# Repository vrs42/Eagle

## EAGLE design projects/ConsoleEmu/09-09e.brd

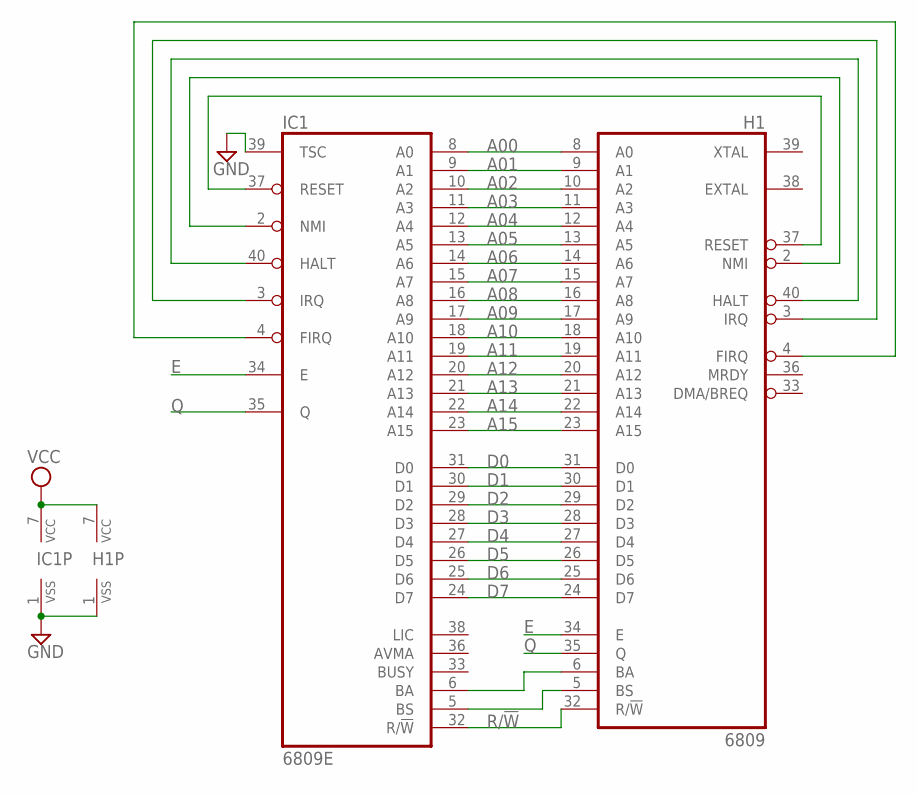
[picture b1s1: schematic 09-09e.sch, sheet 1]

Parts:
H1: 6809; DIL40
IC1: 6809E; DIL40

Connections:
A00: H1.8 (A0), IC1.8 (A0)
A01: H1.9 (A1), IC1.9 (A1)
A02: H1.10 (A2), IC1.10 (A2)
A03: H1.11 (A3), IC1.11 (A3)
A04: H1.12 (A4), IC1.12 (A4)
A05: H1.13 (A5), IC1.13 (A5)
A06: H1.14 (A6), IC1.14 (A6)
A07: H1.15 (A7), IC1.15 (A7)
A08: H1.16 (A8), IC1.16 (A8)
A09: H1.17 (A9), IC1.17 (A9)
A10: H1.18 (A10), IC1.18 (A10)
A11: H1.19 (A11), IC1.19 (A11)
A12: H1.20 (A12), IC1.20 (A12)
A13: H1.21 (A13), IC1.21 (A13)
A14: H1.22 (A14), IC1.22 (A14)
A15: H1.23 (A15), IC1.23 (A15)
D0: H1.31 (D0), IC1.31 (D0)
D1: H1.30 (D1), IC1.30 (D1)
D2: H1.29 (D2), IC1.29 (D2)
D3: H1.28 (D3), IC1.28 (D3)
D4: H1.27 (D4), IC1.27 (D4)
D5: H1.26 (D5), IC1.26 (D5)
D6: H1.25 (D6), IC1.25 (D6)
D7: H1.24 (D7), IC1.24 (D7)
E: H1.34 (E), IC1.34 (E); also elsewhere on the board
GND: H1.1 (VSS), IC1.1 (VSS), IC1.39 (TSC); also elsewhere on the board
unnamed: H1.5 (BS), IC1.5 (BS)
unnamed: H1.6 (BA), IC1.6 (BA)
unnamed: H1.37 (RESET), IC1.37 (RESET)
unnamed: H1.2 (NMI), IC1.2 (NMI)
unnamed: H1.40 (HALT), IC1.40 (HALT)
unnamed: H1.3 (IRQ), IC1.3 (IRQ)
unnamed: H1.4 (FIRQ), IC1.4 (FIRQ)
Q: H1.35 (Q), IC1.35 (Q); also elsewhere on the board
R/!W: H1.32 (R/!W), IC1.32 (R/!W)
VCC: H1.7 (VCC), IC1.7 (VCC); also elsewhere on the board

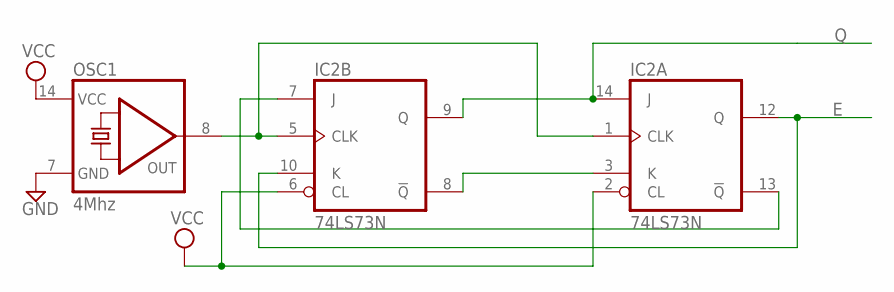
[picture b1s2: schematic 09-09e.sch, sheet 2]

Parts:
IC2: 74LS73N; DIL14
OSC1: 4Mhz; DIL14S

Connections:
E: IC2.10 (K), IC2.12 (Q); also elsewhere on the board
GND: IC2.11 (GND), OSC1.7 (GND); also elsewhere on the board
unnamed: IC2.1 (CLK), IC2.5 (CLK), OSC1.8 (OUT)
unnamed: IC2.3 (K), IC2.8 (!Q)
unnamed: IC2.7 (J), IC2.13 (!Q)
Q: IC2.9 (Q), IC2.14 (J); also elsewhere on the board
VCC: IC2.2 (CL), IC2.4 (VCC), IC2.6 (CL), OSC1.14 (VCC); also elsewhere on the board

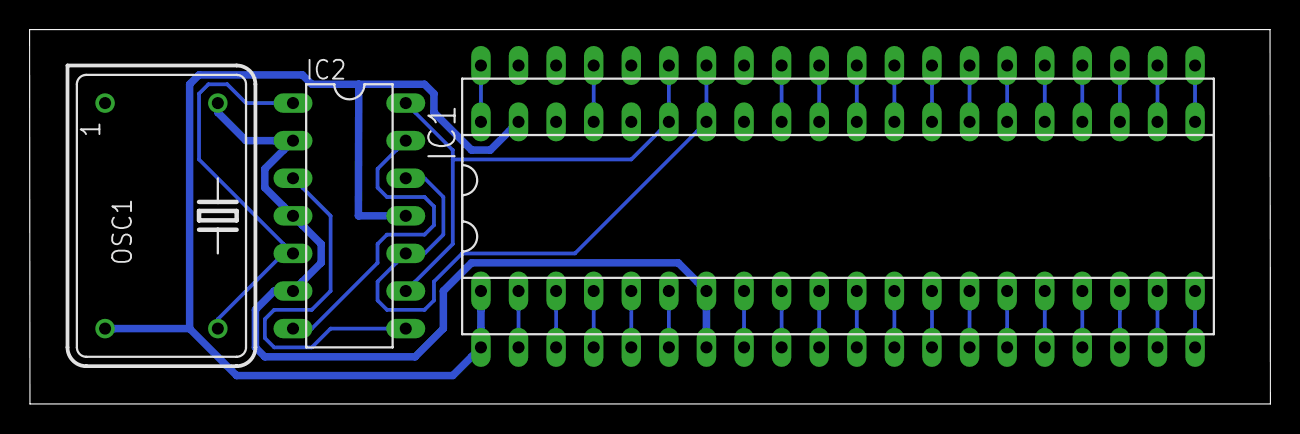
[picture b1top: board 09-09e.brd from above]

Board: 2 copper layers, 83.9 x 25.3 mm, 4 parts (0 on the bottom side), 39 nets.

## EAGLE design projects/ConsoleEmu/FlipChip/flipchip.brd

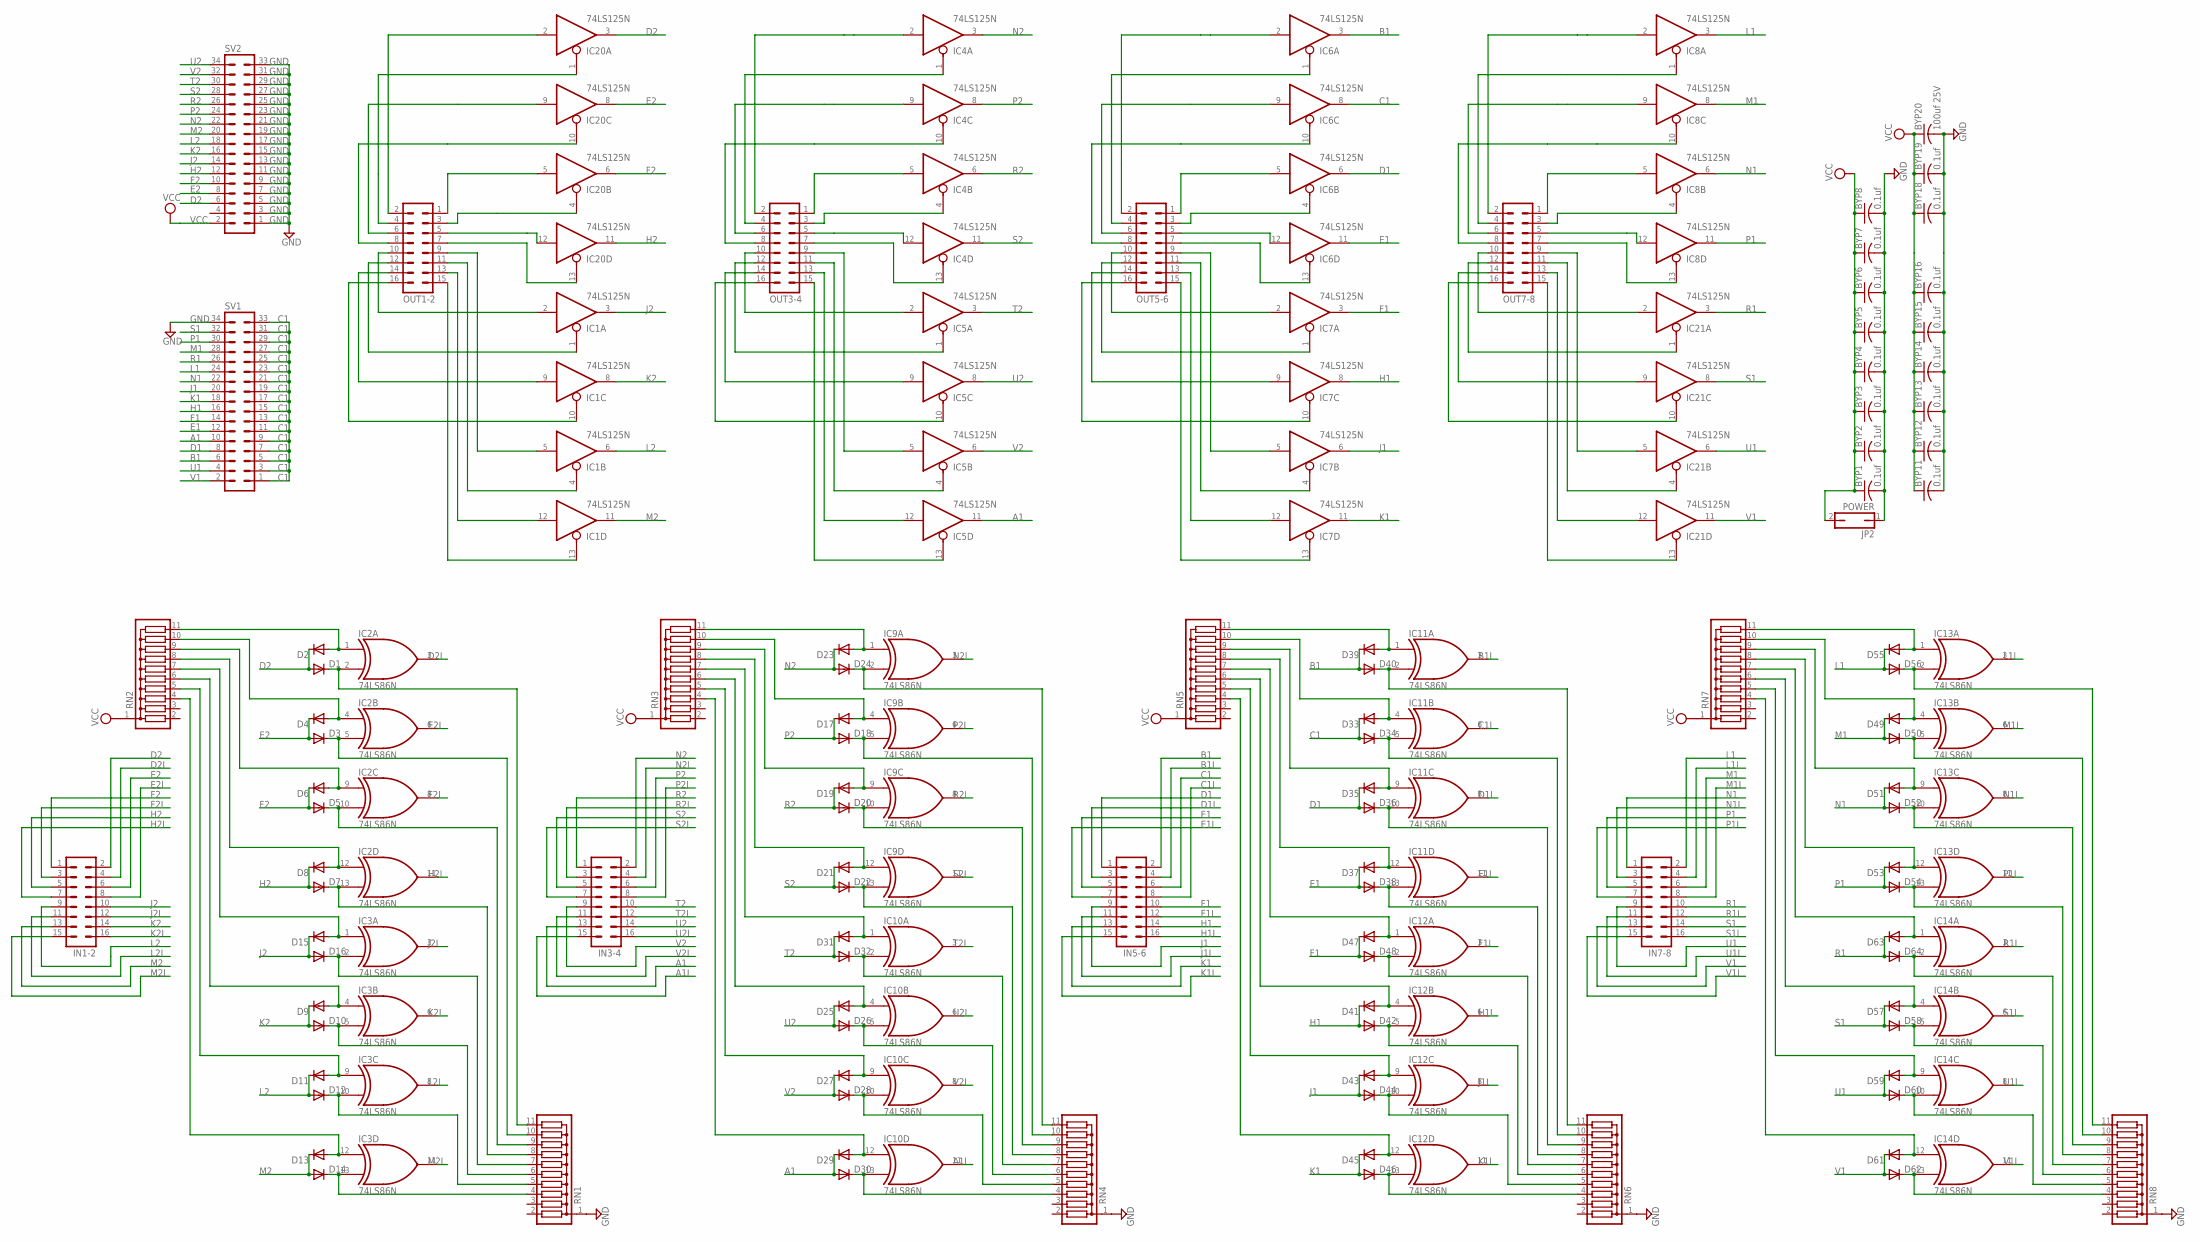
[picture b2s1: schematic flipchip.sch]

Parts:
BYP1, BYP2, BYP3, BYP4, BYP5, BYP6, BYP7, BYP8, BYP11, BYP12, BYP13, BYP14, BYP15, BYP16, BYP18, BYP19: 0.1uf; C050-025X075
BYP20: 100uf 25V; C150-064X183
D1, D2, D3, D4, D5, D6, D7, D8, D9, D10, D11, D12, D13, D14, D15, D16, D17, D18, D19, D20, D21, D22, D23, D24, D25, D26, D27, D28, D29, D30, D31, D32, D33, D34, D35, D36, D37, D38, D39, D40, D41, D42, D43, D44, D45, D46, D47, D48, D49, D50, D51, D52, D53, D54, D55, D56, D57, D58, D59, D60, D61, D62, D63, D64: DIODE-D-2.5; D-2.5
IC1, IC4, IC5, IC6, IC7, IC8, IC20, IC21: 74LS125N; DIL14
IC2, IC3, IC9, IC10, IC11, IC12, IC13, IC14: 74LS86N; DIL14
IN1-2, IN3-4, IN5-6, IN7-8: MA08-2
JP2: POWER; JP1
OUT1-2, OUT3-4, OUT5-6, OUT7-8: MA08-2
RN1, RN2, RN3, RN4, RN5, RN6, RN7, RN8: G10R; SIL11
SV1, SV2: MA17-2

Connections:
A1: D29.C, D30.A, IC5.11 (O), IN3-4.13, SV1.10
A1I: IC10.11 (O), IN3-4.15
B1: D39.C, D40.A, IC6.3 (O), IN5-6.2, SV1.6
B1I: IC11.3 (O), IN5-6.4
C1: D33.C, D34.A, IC6.8 (O), IN5-6.6, SV1.1, SV1.3, SV1.5, SV1.7, SV1.9, SV1.11, SV1.13, SV1.15, SV1.17, SV1.19, SV1.21, SV1.23, SV1.25, SV1.27, SV1.29, SV1.31, SV1.33
C1I: IC11.6 (O), IN5-6.8
D1: D35.C, D36.A, IC6.6 (O), IN5-6.1, SV1.8
D1I: IC11.8 (O), IN5-6.3
D2: D1.A, D2.C, IC20.3 (O), IN1-2.2, SV2.6
D2I: IC2.3 (O), IN1-2.4
E1: D37.C, D38.A, IC6.11 (O), IN5-6.5, SV1.12
E1I: IC11.11 (O), IN5-6.7
E2: D3.A, D4.C, IC20.8 (O), IN1-2.6, SV2.8
E2I: IC2.6 (O), IN1-2.8
F1: D47.C, D48.A, IC7.3 (O), IN5-6.10, SV1.14
F1I: IC12.3 (O), IN5-6.12
F2: D5.A, D6.C, IC20.6 (O), IN1-2.1, SV2.10
F2I: IC2.8 (O), IN1-2.3
GND: BYP1.2, BYP2.2, BYP3.2, BYP4.2, BYP5.2, BYP6.2, BYP7.2, BYP8.2, BYP11.2, BYP12.2, BYP13.2, BYP14.2, BYP15.2, BYP16.2, BYP18.2, BYP19.2, BYP20.2, IC1.7 (GND), IC2.7 (GND), IC3.7 (GND), IC4.7 (GND), IC5.7 (GND), IC6.7 (GND), IC7.7 (GND), IC8.7 (GND), IC9.7 (GND), IC10.7 (GND), IC11.7 (GND), IC12.7 (GND), IC13.7 (GND), IC14.7 (GND), IC20.7 (GND), IC21.7 (GND), JP2.1, RN1.1, RN4.1, RN6.1, RN8.1, SV1.34, SV2.1, SV2.3, SV2.5, SV2.7, SV2.9, SV2.11, SV2.13, SV2.15, SV2.17, SV2.19, SV2.21, SV2.23, SV2.25, SV2.27, SV2.29, SV2.31, SV2.33
H1: D41.C, D42.A, IC7.8 (O), IN5-6.14, SV1.16
H1I: IC12.6 (O), IN5-6.16
H2: D7.A, D8.C, IC20.11 (O), IN1-2.5, SV2.12
H2I: IC2.11 (O), IN1-2.7
J1: D43.C, D44.A, IC7.6 (O), IN5-6.9, SV1.20
J1I: IC12.8 (O), IN5-6.11
J2: D15.C, D16.A, IC1.3 (O), IN1-2.10, SV2.14
J2I: IC3.3 (O), IN1-2.12
K1: D45.C, D46.A, IC7.11 (O), IN5-6.13, SV1.18
K1I: IC12.11 (O), IN5-6.15
K2: D9.C, D10.A, IC1.8 (O), IN1-2.14, SV2.16
K2I: IC3.6 (O), IN1-2.16
L1: D55.C, D56.A, IC8.3 (O), IN7-8.2, SV1.24
L1I: IC13.3 (O), IN7-8.4
L2: D11.C, D12.A, IC1.6 (O), IN1-2.9, SV2.18
L2I: IC3.8 (O), IN1-2.11
M1: D49.C, D50.A, IC8.8 (O), IN7-8.6, SV1.28
M1I: IC13.6 (O), IN7-8.8
M2: D13.C, D14.A, IC1.11 (O), IN1-2.13, SV2.20
M2I: IC3.11 (O), IN1-2.15
N1: D51.C, D52.A, IC8.6 (O), IN7-8.1, SV1.22
N1I: IC13.8 (O), IN7-8.3
N2: D23.C, D24.A, IC4.3 (O), IN3-4.2, SV2.22
N2I: IC9.3 (O), IN3-4.4
unnamed: D24.C, IC9.2 (I1), RN4.11
unnamed: D23.A, IC9.1 (I0), RN3.11
unnamed: D1.C, IC2.2 (I1), RN1.11
unnamed: D2.A, IC2.1 (I0), RN2.11
unnamed: D18.C, IC9.5 (I1), RN4.10
unnamed: D3.C, IC2.5 (I1), RN1.10
unnamed: D17.A, IC9.4 (I0), RN3.10
unnamed: D19.A, IC9.9 (I0), RN3.9
unnamed: D21.A, IC9.12 (I0), RN3.8
unnamed: D31.A, IC10.1 (I0), RN3.7
unnamed: D25.A, IC10.4 (I0), RN3.6
unnamed: D27.A, IC10.9 (I0), RN3.5
unnamed: D29.A, IC10.12 (I0), RN3.4
unnamed: D28.C, IC10.10 (I1), RN4.5
unnamed: D20.C, IC9.10 (I1), RN4.9
unnamed: D22.C, IC9.13 (I1), RN4.8
unnamed: D32.C, IC10.2 (I1), RN4.7
unnamed: D26.C, IC10.5 (I1), RN4.6
unnamed: D30.C, IC10.13 (I1), RN4.4
unnamed: D40.C, IC11.2 (I1), RN6.11
unnamed: D4.A, IC2.4 (I0), RN2.10
unnamed: D39.A, IC11.1 (I0), RN5.11
unnamed: D5.C, IC2.10 (I1), RN1.9
unnamed: D6.A, IC2.9 (I0), RN2.9
unnamed: D34.C, IC11.5 (I1), RN6.10
unnamed: IC6.2 (I), OUT5-6.2
unnamed: IC4.5 (I), OUT3-4.1
unnamed: IC4.4 (OE), OUT3-4.3
unnamed: IC4.12 (I), OUT3-4.5
unnamed: IC4.13 (OE), OUT3-4.7
unnamed: IC4.1 (OE), OUT3-4.4
unnamed: IC4.9 (I), OUT3-4.6
unnamed: IC4.2 (I), OUT3-4.2
unnamed: IC4.10 (OE), OUT3-4.8
unnamed: IC20.5 (I), OUT1-2.1
unnamed: IC20.4 (OE), OUT1-2.3
unnamed: IC20.12 (I), OUT1-2.5
unnamed: IC20.13 (OE), OUT1-2.7
unnamed: IC20.2 (I), OUT1-2.2
unnamed: IC20.1 (OE), OUT1-2.4
unnamed: IC20.9 (I), OUT1-2.6
unnamed: IC20.10 (OE), OUT1-2.8
unnamed: IC1.13 (OE), OUT1-2.15
unnamed: IC1.12 (I), OUT1-2.13
unnamed: IC1.4 (OE), OUT1-2.11
unnamed: IC1.5 (I), OUT1-2.9
unnamed: IC1.2 (I), OUT1-2.10
unnamed: IC1.1 (OE), OUT1-2.12
unnamed: IC1.9 (I), OUT1-2.14
unnamed: IC1.10 (OE), OUT1-2.16
unnamed: IC5.2 (I), OUT3-4.10
unnamed: IC5.1 (OE), OUT3-4.12
unnamed: IC5.9 (I), OUT3-4.14
unnamed: IC5.10 (OE), OUT3-4.16
unnamed: IC5.13 (OE), OUT3-4.15
unnamed: IC5.12 (I), OUT3-4.13
unnamed: IC5.4 (OE), OUT3-4.11
unnamed: IC5.5 (I), OUT3-4.9
unnamed: IC6.5 (I), OUT5-6.1
unnamed: IC6.4 (OE), OUT5-6.3
unnamed: IC6.12 (I), OUT5-6.5
unnamed: IC6.13 (OE), OUT5-6.7
unnamed: IC8.5 (I), OUT7-8.1
unnamed: IC8.4 (OE), OUT7-8.3
unnamed: IC8.12 (I), OUT7-8.5
unnamed: IC8.13 (OE), OUT7-8.7
unnamed: IC6.1 (OE), OUT5-6.4
unnamed: IC6.9 (I), OUT5-6.6
unnamed: IC6.10 (OE), OUT5-6.8
unnamed: IC7.5 (I), OUT5-6.9
unnamed: IC7.4 (OE), OUT5-6.11
unnamed: IC7.12 (I), OUT5-6.13
unnamed: IC7.13 (OE), OUT5-6.15
unnamed: IC7.2 (I), OUT5-6.10
unnamed: IC7.1 (OE), OUT5-6.12
unnamed: IC7.9 (I), OUT5-6.14
unnamed: IC7.10 (OE), OUT5-6.16
unnamed: IC21.13 (OE), OUT7-8.15
unnamed: IC21.12 (I), OUT7-8.13
unnamed: IC21.4 (OE), OUT7-8.11
unnamed: IC21.5 (I), OUT7-8.9
unnamed: IC21.2 (I), OUT7-8.10
unnamed: IC21.1 (OE), OUT7-8.12
unnamed: IC21.9 (I), OUT7-8.14
unnamed: IC21.10 (OE), OUT7-8.16
unnamed: IC8.10 (OE), OUT7-8.8
unnamed: IC8.9 (I), OUT7-8.6
unnamed: IC8.1 (OE), OUT7-8.4
unnamed: IC8.2 (I), OUT7-8.2
unnamed: D7.C, IC2.13 (I1), RN1.8
unnamed: D8.A, IC2.12 (I0), RN2.8
unnamed: D33.A, IC11.4 (I0), RN5.10
unnamed: D16.C, IC3.2 (I1), RN1.7
unnamed: D15.A, IC3.1 (I0), RN2.7
unnamed: D35.A, IC11.9 (I0), RN5.9
unnamed: D10.C, IC3.5 (I1), RN1.6
unnamed: D9.A, IC3.4 (I0), RN2.6
unnamed: D37.A, IC11.12 (I0), RN5.8
unnamed: D12.C, IC3.10 (I1), RN1.5
unnamed: D11.A, IC3.9 (I0), RN2.5
unnamed: D47.A, IC12.1 (I0), RN5.7
unnamed: D14.C, IC3.13 (I1), RN1.4
unnamed: D13.A, IC3.12 (I0), RN2.4
unnamed: D41.A, IC12.4 (I0), RN5.6
unnamed: D43.A, IC12.9 (I0), RN5.5
unnamed: D45.A, IC12.12 (I0), RN5.4
unnamed: D44.C, IC12.10 (I1), RN6.5
unnamed: D36.C, IC11.10 (I1), RN6.9
unnamed: D38.C, IC11.13 (I1), RN6.8
unnamed: D48.C, IC12.2 (I1), RN6.7
unnamed: D42.C, IC12.5 (I1), RN6.6
unnamed: D46.C, IC12.13 (I1), RN6.4
unnamed: D56.C, IC13.2 (I1), RN8.11
unnamed: D55.A, IC13.1 (I0), RN7.11
unnamed: D50.C, IC13.5 (I1), RN8.10
unnamed: D49.A, IC13.4 (I0), RN7.10
unnamed: D51.A, IC13.9 (I0), RN7.9
unnamed: D53.A, IC13.12 (I0), RN7.8
unnamed: D63.A, IC14.1 (I0), RN7.7
unnamed: D57.A, IC14.4 (I0), RN7.6
unnamed: D59.A, IC14.9 (I0), RN7.5
unnamed: D61.A, IC14.12 (I0), RN7.4
unnamed: D60.C, IC14.10 (I1), RN8.5
unnamed: D52.C, IC13.10 (I1), RN8.9
unnamed: D54.C, IC13.13 (I1), RN8.8
unnamed: D64.C, IC14.2 (I1), RN8.7
unnamed: D58.C, IC14.5 (I1), RN8.6
unnamed: D62.C, IC14.13 (I1), RN8.4
P1: D53.C, D54.A, IC8.11 (O), IN7-8.5, SV1.30
P1I: IC13.11 (O), IN7-8.7
P2: D17.C, D18.A, IC4.8 (O), IN3-4.6, SV2.24
P2I: IC9.6 (O), IN3-4.8
R1: D63.C, D64.A, IC21.3 (O), IN7-8.10, SV1.26
R1I: IC14.3 (O), IN7-8.12
R2: D19.C, D20.A, IC4.6 (O), IN3-4.1, SV2.26
R2I: IC9.8 (O), IN3-4.3
S1: D57.C, D58.A, IC21.8 (O), IN7-8.14, SV1.32
S1I: IC14.6 (O), IN7-8.16
S2: D21.C, D22.A, IC4.11 (O), IN3-4.5, SV2.28
S2I: IC9.11 (O), IN3-4.7
T2: D31.C, D32.A, IC5.3 (O), IN3-4.10, SV2.30
T2I: IC10.3 (O), IN3-4.12
U1: D59.C, D60.A, IC21.6 (O), IN7-8.9, SV1.4
U1I: IC14.8 (O), IN7-8.11
U2: D25.C, D26.A, IC5.8 (O), IN3-4.14, SV2.34
U2I: IC10.6 (O), IN3-4.16
V1: D61.C, D62.A, IC21.11 (O), IN7-8.13, SV1.2
V1I: IC14.11 (O), IN7-8.15
V2: D27.C, D28.A, IC5.6 (O), IN3-4.9, SV2.32
V2I: IC10.8 (O), IN3-4.11
VCC: BYP1.1, BYP2.1, BYP3.1, BYP4.1, BYP5.1, BYP6.1, BYP7.1, BYP8.1, BYP11.1, BYP12.1, BYP13.1, BYP14.1, BYP15.1, BYP16.1, BYP18.1, BYP19.1, BYP20.1, IC1.14 (VCC), IC2.14 (VCC), IC3.14 (VCC), IC4.14 (VCC), IC5.14 (VCC), IC6.14 (VCC), IC7.14 (VCC), IC8.14 (VCC), IC9.14 (VCC), IC10.14 (VCC), IC11.14 (VCC), IC12.14 (VCC), IC13.14 (VCC), IC14.14 (VCC), IC20.14 (VCC), IC21.14 (VCC), JP2.2, RN2.1, RN3.1, RN5.1, RN7.1, SV2.2

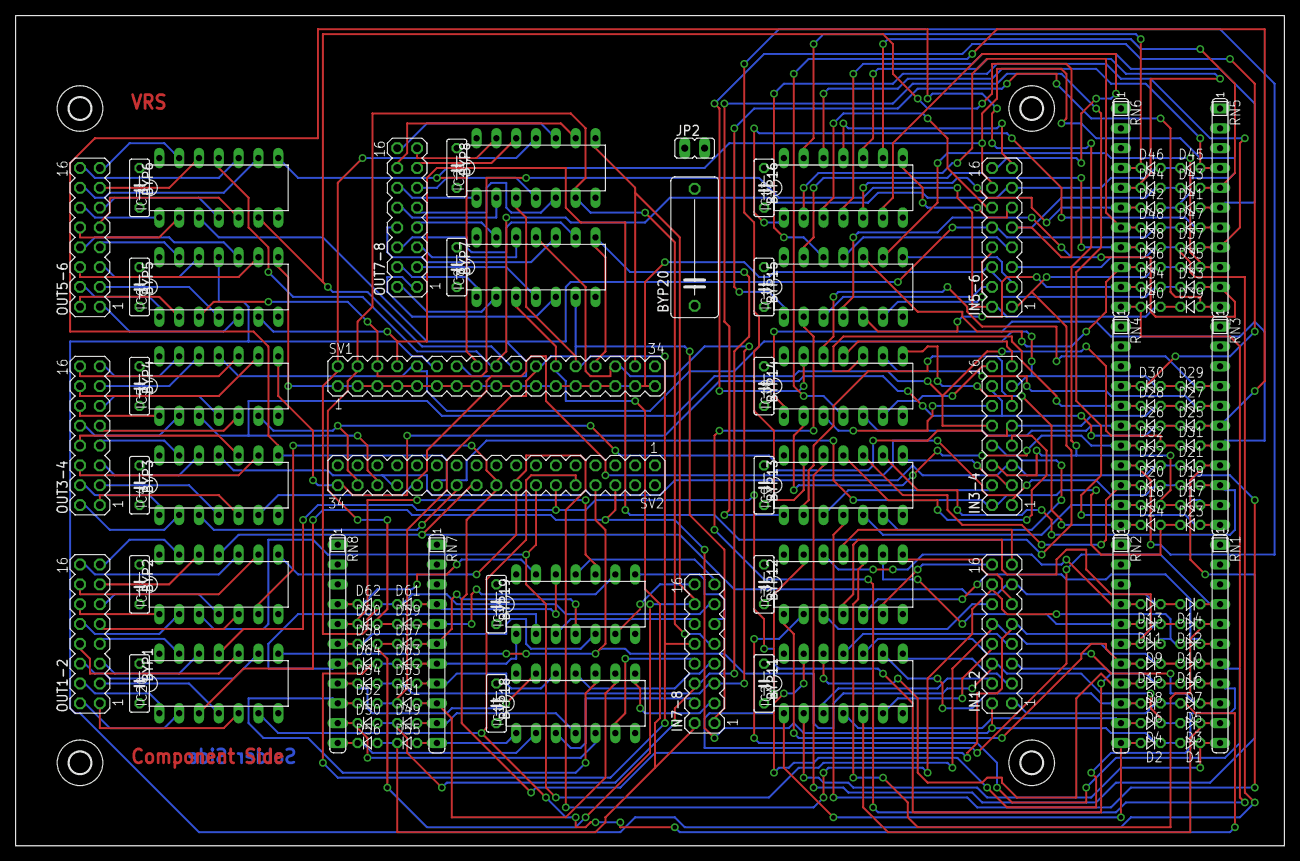
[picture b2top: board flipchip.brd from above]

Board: 4 copper layers, 162.5 x 106.4 mm, 120 parts (0 on the bottom side), 194 nets.

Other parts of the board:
U$1, U$2, U$3, U$4: 2,8

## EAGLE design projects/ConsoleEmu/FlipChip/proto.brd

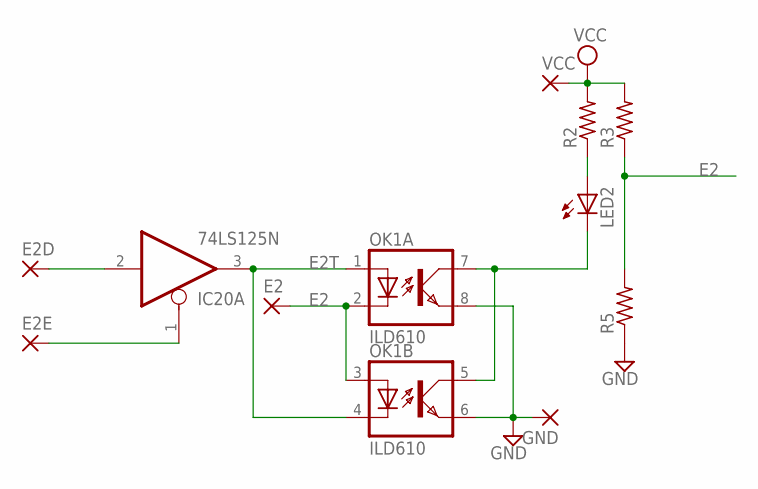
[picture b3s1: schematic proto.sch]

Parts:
E2, E2D, E2E: 1,6/0,9
GND: 1,6/0,9
IC20: 74LS125N; DIL14
LED2: LED5MM
OK1: ILD610; DIL08
R2, R3, R5: R-US_0207/10; 0207/10
VCC: 1,6/0,9

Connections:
E2: E2.1, OK1.2 (C), OK1.3 (A), R3.1, R5.2
E2T: IC20.3 (O), OK1.1 (A), OK1.4 (C)
GND: GND.1, IC20.7 (GND), OK1.6 (EMIT), OK1.8 (EMIT), R5.1
unnamed: LED2.K (C), OK1.5 (COL), OK1.7 (COL)
unnamed: LED2.A, R2.1
unnamed: E2D.1, IC20.2 (I)
unnamed: E2E.1, IC20.1 (OE)
VCC: IC20.14 (VCC), R2.2, R3.2, VCC.1

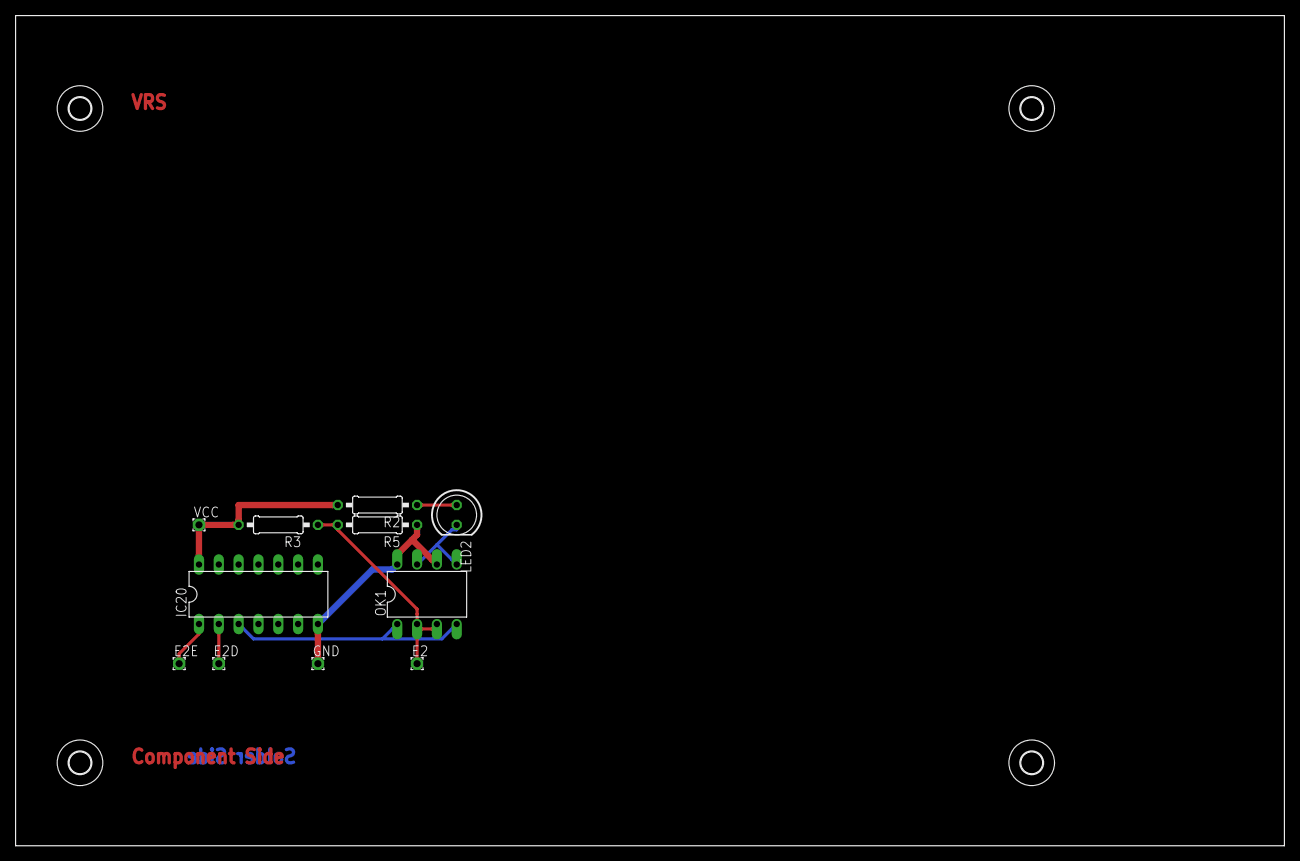
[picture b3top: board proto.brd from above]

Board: 2 copper layers, 162.5 x 106.4 mm, 15 parts (0 on the bottom side), 8 nets.

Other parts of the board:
U$1, U$2, U$3, U$4: 2,8

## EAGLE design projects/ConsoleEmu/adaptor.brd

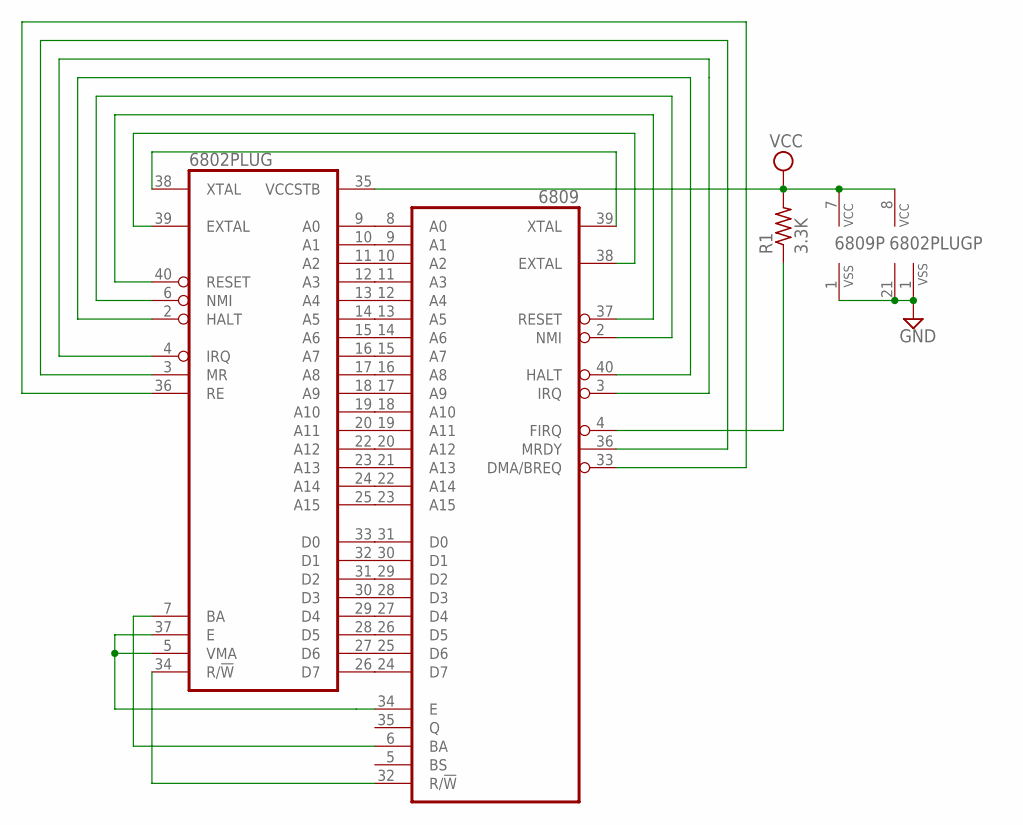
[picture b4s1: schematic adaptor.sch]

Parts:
6802PLUG: 6802; DIL40
6809: 6809; DIL40
R1: 3.3K; 0207/10

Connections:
GND: 6802PLUG.1 (VSS), 6802PLUG.21 (VSS), 6809.1 (VSS)
unnamed: 6802PLUG.9 (A0), 6809.8 (A0)
unnamed: 6802PLUG.10 (A1), 6809.9 (A1)
unnamed: 6802PLUG.11 (A2), 6809.10 (A2)
unnamed: 6802PLUG.12 (A3), 6809.11 (A3)
unnamed: 6802PLUG.13 (A4), 6809.12 (A4)
unnamed: 6802PLUG.14 (A5), 6809.13 (A5)
unnamed: 6802PLUG.15 (A6), 6809.14 (A6)
unnamed: 6802PLUG.16 (A7), 6809.15 (A7)
unnamed: 6802PLUG.17 (A8), 6809.16 (A8)
unnamed: 6802PLUG.18 (A9), 6809.17 (A9)
unnamed: 6802PLUG.19 (A10), 6809.18 (A10)
unnamed: 6802PLUG.20 (A11), 6809.19 (A11)
unnamed: 6802PLUG.22 (A12), 6809.20 (A12)
unnamed: 6802PLUG.23 (A13), 6809.21 (A13)
unnamed: 6802PLUG.24 (A14), 6809.22 (A14)
unnamed: 6802PLUG.25 (A15), 6809.23 (A15)
unnamed: 6802PLUG.26 (D7), 6809.24 (D7)
unnamed: 6802PLUG.27 (D6), 6809.25 (D6)
unnamed: 6802PLUG.28 (D5), 6809.26 (D5)
unnamed: 6802PLUG.29 (D4), 6809.27 (D4)
unnamed: 6802PLUG.30 (D3), 6809.28 (D3)
unnamed: 6802PLUG.31 (D2), 6809.29 (D2)
unnamed: 6802PLUG.32 (D1), 6809.30 (D1)
unnamed: 6802PLUG.33 (D0), 6809.31 (D0)
unnamed: 6802PLUG.34 (R/!W), 6809.32 (R/!W)
unnamed: 6802PLUG.7 (BA), 6809.6 (BA)
unnamed: 6802PLUG.5 (VMA), 6802PLUG.37 (E), 6809.34 (E)
unnamed: 6802PLUG.38 (XTAL), 6809.39 (XTAL)
unnamed: 6802PLUG.39 (EXTAL), 6809.38 (EXTAL)
unnamed: 6802PLUG.40 (RESET), 6809.37 (RESET)
unnamed: 6802PLUG.6 (NMI), 6809.2 (NMI)
unnamed: 6802PLUG.2 (HALT), 6809.40 (HALT)
unnamed: 6802PLUG.4 (IRQ), 6809.3 (IRQ)
unnamed: 6802PLUG.3 (MR), 6809.36 (MRDY)
unnamed: 6802PLUG.36 (RE), 6809.33 (DMA/BREQ)
unnamed: 6809.4 (FIRQ), R1.1
VCC: 6802PLUG.8 (VCC), 6802PLUG.35 (VCCSTB), 6809.7 (VCC), R1.2

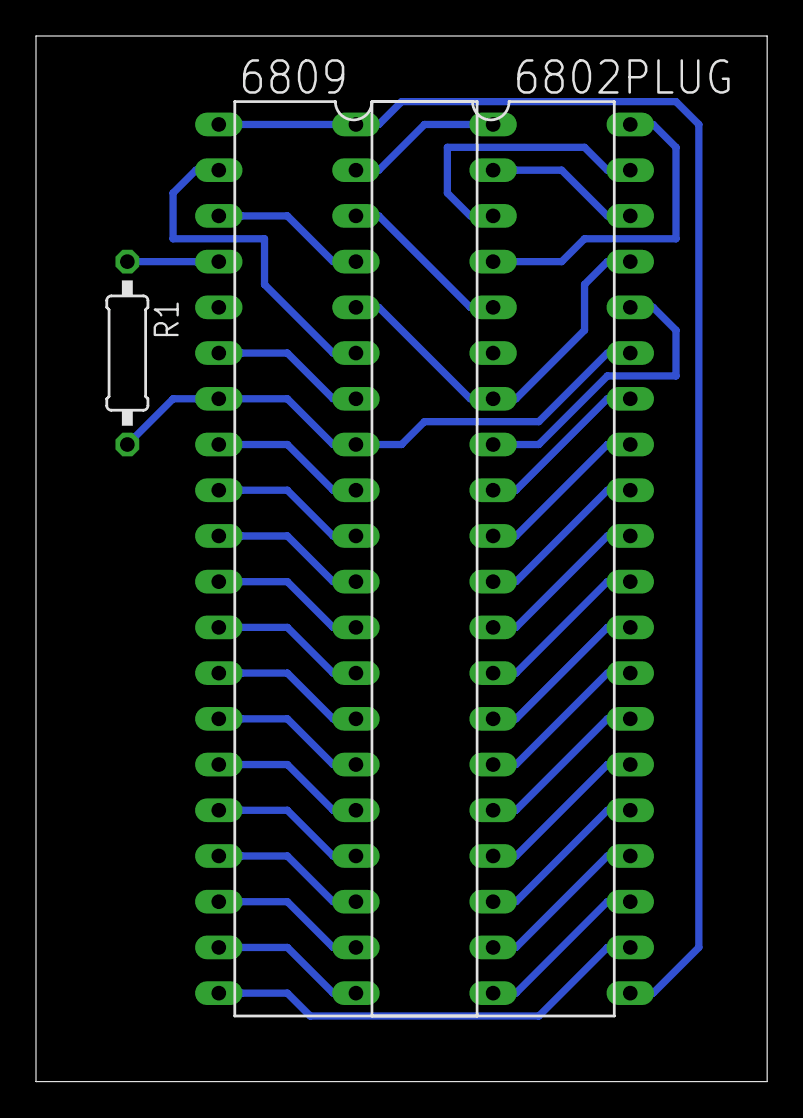
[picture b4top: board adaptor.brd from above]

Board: 2 copper layers, 40.6 x 58.1 mm, 3 parts (0 on the bottom side), 38 nets.

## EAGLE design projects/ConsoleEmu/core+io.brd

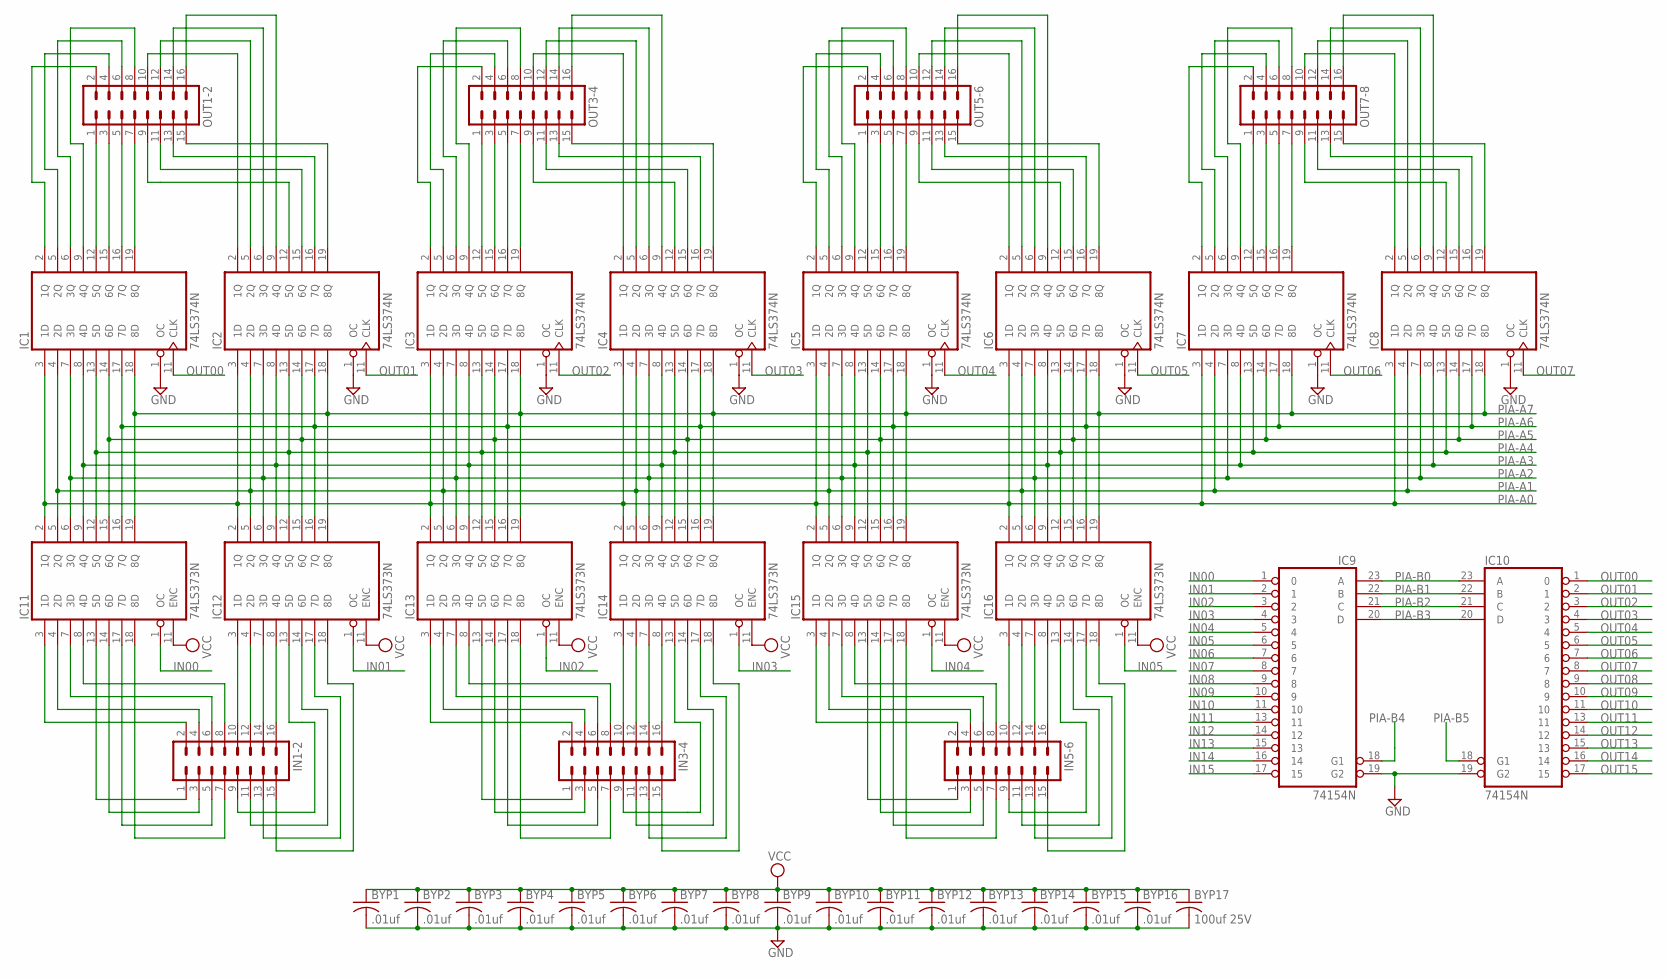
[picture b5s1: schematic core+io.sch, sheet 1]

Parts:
BYP1, BYP2, BYP3, BYP4, BYP5, BYP6, BYP7, BYP8, BYP9, BYP10, BYP11, BYP12, BYP13, BYP14, BYP15, BYP16: .01uf; C050-025X075
BYP17: 100uf 25V; C102-043X133
IC1, IC2, IC3, IC4, IC5, IC6, IC7, IC8: 74LS374N; DIL20
IC9, IC10: 74154N; DIL24-6
IC11, IC12, IC13, IC14, IC15, IC16: 74LS373N; DIL20
IN1-2, IN3-4, IN5-6: MA08-2
OUT1-2, OUT3-4, OUT5-6, OUT7-8: MA08-2

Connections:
GND: BYP1.2, BYP2.2, BYP3.2, BYP4.2, BYP5.2, BYP6.2, BYP7.2, BYP8.2, BYP9.2, BYP10.2, BYP11.2, BYP12.2, BYP13.2, BYP14.2, BYP15.2, BYP16.2, BYP17.2, IC1.1 (OC), IC1.10 (GND), IC2.1 (OC), IC2.10 (GND), IC3.1 (OC), IC3.10 (GND), IC4.1 (OC), IC4.10 (GND), IC5.1 (OC), IC5.10 (GND), IC6.1 (OC), IC6.10 (GND), IC7.1 (OC), IC7.10 (GND), IC8.1 (OC), IC8.10 (GND), IC9.12 (GND), IC9.19 (G2), IC10.12 (GND), IC10.19 (G2), IC11.10 (GND), IC12.10 (GND), IC13.10 (GND), IC14.10 (GND), IC15.10 (GND), IC16.10 (GND); also elsewhere on the board
IN00: IC9.1 (0), IC11.1 (OC)
IN01: IC9.2 (1), IC12.1 (OC)
IN02: IC9.3 (2), IC13.1 (OC)
IN03: IC9.4 (3), IC14.1 (OC)
IN04: IC9.5 (4), IC15.1 (OC)
IN05: IC9.6 (5), IC16.1 (OC)
IN06: IC9.7 (6)
IN07: IC9.8 (7)
IN08: IC9.9 (8)
IN09: IC9.10 (9)
IN10: IC9.11 (10)
IN11: IC9.13 (11)
IN12: IC9.14 (12)
IN13: IC9.15 (13)
IN14: IC9.16 (14)
IN15: IC9.17 (15)
unnamed: IC12.3 (1D), IN1-2.10
unnamed: IC12.4 (2D), IN1-2.12
unnamed: IC12.7 (3D), IN1-2.14
unnamed: IC12.8 (4D), IN1-2.16
unnamed: IC11.8 (4D), IN1-2.8
unnamed: IC11.7 (3D), IN1-2.6
unnamed: IC11.4 (2D), IN1-2.4
unnamed: IC11.3 (1D), IN1-2.2
unnamed: IC11.13 (5D), IN1-2.1
unnamed: IC11.14 (6D), IN1-2.3
unnamed: IC11.17 (7D), IN1-2.5
unnamed: IC11.18 (8D), IN1-2.7
unnamed: IC12.13 (5D), IN1-2.9
unnamed: IC12.14 (6D), IN1-2.11
unnamed: IC12.17 (7D), IN1-2.13
unnamed: IC12.18 (8D), IN1-2.15
unnamed: IC5.2 (1Q), OUT5-6.2
unnamed: IC14.3 (1D), IN3-4.10
unnamed: IC14.4 (2D), IN3-4.12
unnamed: IC14.7 (3D), IN3-4.14
unnamed: IC14.8 (4D), IN3-4.16
unnamed: IC3.12 (5Q), OUT3-4.1
unnamed: IC3.15 (6Q), OUT3-4.3
unnamed: IC3.16 (7Q), OUT3-4.5
unnamed: IC3.19 (8Q), OUT3-4.7
unnamed: IC13.3 (1D), IN3-4.2
unnamed: IC13.4 (2D), IN3-4.4
unnamed: IC13.7 (3D), IN3-4.6
unnamed: IC13.8 (4D), IN3-4.8
unnamed: IC14.13 (5D), IN3-4.9
unnamed: IC14.14 (6D), IN3-4.11
unnamed: IC14.17 (7D), IN3-4.13
unnamed: IC14.18 (8D), IN3-4.15
unnamed: IC13.13 (5D), IN3-4.1
unnamed: IC13.14 (6D), IN3-4.3
unnamed: IC13.17 (7D), IN3-4.5
unnamed: IC13.18 (8D), IN3-4.7
unnamed: IC3.5 (2Q), OUT3-4.4
unnamed: IC3.6 (3Q), OUT3-4.6
unnamed: IC3.2 (1Q), OUT3-4.2
unnamed: IC3.9 (4Q), OUT3-4.8
unnamed: IC1.12 (5Q), OUT1-2.1
unnamed: IC1.15 (6Q), OUT1-2.3
unnamed: IC1.16 (7Q), OUT1-2.5
unnamed: IC1.19 (8Q), OUT1-2.7
unnamed: IC1.2 (1Q), OUT1-2.2
unnamed: IC1.5 (2Q), OUT1-2.4
unnamed: IC1.6 (3Q), OUT1-2.6
unnamed: IC1.9 (4Q), OUT1-2.8
unnamed: IC2.19 (8Q), OUT1-2.15
unnamed: IC2.16 (7Q), OUT1-2.13
unnamed: IC2.15 (6Q), OUT1-2.11
unnamed: IC2.12 (5Q), OUT1-2.9
unnamed: IC2.2 (1Q), OUT1-2.10
unnamed: IC2.5 (2Q), OUT1-2.12
unnamed: IC2.6 (3Q), OUT1-2.14
unnamed: IC2.9 (4Q), OUT1-2.16
unnamed: IC4.2 (1Q), OUT3-4.10
unnamed: IC4.5 (2Q), OUT3-4.12
unnamed: IC4.6 (3Q), OUT3-4.14
unnamed: IC4.9 (4Q), OUT3-4.16
unnamed: IC4.19 (8Q), OUT3-4.15
unnamed: IC4.16 (7Q), OUT3-4.13
unnamed: IC4.15 (6Q), OUT3-4.11
unnamed: IC4.12 (5Q), OUT3-4.9
unnamed: IC16.3 (1D), IN5-6.10
unnamed: IC16.4 (2D), IN5-6.12
unnamed: IC16.7 (3D), IN5-6.14
unnamed: IC16.8 (4D), IN5-6.16
unnamed: IC5.12 (5Q), OUT5-6.1
unnamed: IC5.15 (6Q), OUT5-6.3
unnamed: IC5.16 (7Q), OUT5-6.5
unnamed: IC5.19 (8Q), OUT5-6.7
unnamed: IC7.12 (5Q), OUT7-8.1
unnamed: IC7.15 (6Q), OUT7-8.3
unnamed: IC7.16 (7Q), OUT7-8.5
unnamed: IC7.19 (8Q), OUT7-8.7
unnamed: IC5.5 (2Q), OUT5-6.4
unnamed: IC5.6 (3Q), OUT5-6.6
unnamed: IC5.9 (4Q), OUT5-6.8
unnamed: IC6.12 (5Q), OUT5-6.9
unnamed: IC6.15 (6Q), OUT5-6.11
unnamed: IC6.16 (7Q), OUT5-6.13
unnamed: IC6.19 (8Q), OUT5-6.15
unnamed: IC6.2 (1Q), OUT5-6.10
unnamed: IC6.5 (2Q), OUT5-6.12
unnamed: IC6.6 (3Q), OUT5-6.14
unnamed: IC6.9 (4Q), OUT5-6.16
unnamed: IC15.3 (1D), IN5-6.2
unnamed: IC15.4 (2D), IN5-6.4
unnamed: IC15.7 (3D), IN5-6.6
unnamed: IC15.8 (4D), IN5-6.8
unnamed: IC16.13 (5D), IN5-6.9
unnamed: IC16.14 (6D), IN5-6.11
unnamed: IC16.17 (7D), IN5-6.13
unnamed: IC16.18 (8D), IN5-6.15
unnamed: IC15.13 (5D), IN5-6.1
unnamed: IC15.14 (6D), IN5-6.3
unnamed: IC15.17 (7D), IN5-6.5
unnamed: IC15.18 (8D), IN5-6.7
unnamed: IC8.19 (8Q), OUT7-8.15
unnamed: IC8.16 (7Q), OUT7-8.13
unnamed: IC8.15 (6Q), OUT7-8.11
unnamed: IC8.12 (5Q), OUT7-8.9
unnamed: IC8.2 (1Q), OUT7-8.10
unnamed: IC8.5 (2Q), OUT7-8.12
unnamed: IC8.6 (3Q), OUT7-8.14
unnamed: IC8.9 (4Q), OUT7-8.16
unnamed: IC7.9 (4Q), OUT7-8.8
unnamed: IC7.6 (3Q), OUT7-8.6
unnamed: IC7.5 (2Q), OUT7-8.4
unnamed: IC7.2 (1Q), OUT7-8.2
OUT00: IC1.11 (CLK), IC10.1 (0)
OUT01: IC2.11 (CLK), IC10.2 (1)
OUT02: IC3.11 (CLK), IC10.3 (2)
OUT03: IC4.11 (CLK), IC10.4 (3)
OUT04: IC5.11 (CLK), IC10.5 (4)
OUT05: IC6.11 (CLK), IC10.6 (5)
OUT06: IC7.11 (CLK), IC10.7 (6)
OUT07: IC8.11 (CLK), IC10.8 (7)
OUT08: IC10.9 (8)
OUT09: IC10.10 (9)
OUT10: IC10.11 (10)
OUT11: IC10.13 (11)
OUT12: IC10.14 (12)
OUT13: IC10.15 (13)
OUT14: IC10.16 (14)
OUT15: IC10.17 (15)
PIA-A0: IC1.3 (1D), IC2.3 (1D), IC3.3 (1D), IC4.3 (1D), IC5.3 (1D), IC6.3 (1D), IC7.3 (1D), IC8.3 (1D), IC11.2 (1Q), IC12.2 (1Q), IC13.2 (1Q), IC14.2 (1Q), IC15.2 (1Q), IC16.2 (1Q); also elsewhere on the board
PIA-A1: IC1.4 (2D), IC2.4 (2D), IC3.4 (2D), IC4.4 (2D), IC5.4 (2D), IC6.4 (2D), IC7.4 (2D), IC8.4 (2D), IC11.5 (2Q), IC12.5 (2Q), IC13.5 (2Q), IC14.5 (2Q), IC15.5 (2Q), IC16.5 (2Q); also elsewhere on the board
PIA-A2: IC1.7 (3D), IC2.7 (3D), IC3.7 (3D), IC4.7 (3D), IC5.7 (3D), IC6.7 (3D), IC7.7 (3D), IC8.7 (3D), IC11.6 (3Q), IC12.6 (3Q), IC13.6 (3Q), IC14.6 (3Q), IC15.6 (3Q), IC16.6 (3Q); also elsewhere on the board
PIA-A3: IC1.8 (4D), IC2.8 (4D), IC3.8 (4D), IC4.8 (4D), IC5.8 (4D), IC6.8 (4D), IC7.8 (4D), IC8.8 (4D), IC11.9 (4Q), IC12.9 (4Q), IC13.9 (4Q), IC14.9 (4Q), IC15.9 (4Q), IC16.9 (4Q); also elsewhere on the board
PIA-A4: IC1.13 (5D), IC2.13 (5D), IC3.13 (5D), IC4.13 (5D), IC5.13 (5D), IC6.13 (5D), IC7.13 (5D), IC8.13 (5D), IC11.12 (5Q), IC12.12 (5Q), IC13.12 (5Q), IC14.12 (5Q), IC15.12 (5Q), IC16.12 (5Q); also elsewhere on the board
PIA-A5: IC1.14 (6D), IC2.14 (6D), IC3.14 (6D), IC4.14 (6D), IC5.14 (6D), IC6.14 (6D), IC7.14 (6D), IC8.14 (6D), IC11.15 (6Q), IC12.15 (6Q), IC13.15 (6Q), IC14.15 (6Q), IC15.15 (6Q), IC16.15 (6Q); also elsewhere on the board
PIA-A6: IC1.17 (7D), IC2.17 (7D), IC3.17 (7D), IC4.17 (7D), IC5.17 (7D), IC6.17 (7D), IC7.17 (7D), IC8.17 (7D), IC11.16 (7Q), IC12.16 (7Q), IC13.16 (7Q), IC14.16 (7Q), IC15.16 (7Q), IC16.16 (7Q); also elsewhere on the board
PIA-A7: IC1.18 (8D), IC2.18 (8D), IC3.18 (8D), IC4.18 (8D), IC5.18 (8D), IC6.18 (8D), IC7.18 (8D), IC8.18 (8D), IC11.19 (8Q), IC12.19 (8Q), IC13.19 (8Q), IC14.19 (8Q), IC15.19 (8Q), IC16.19 (8Q); also elsewhere on the board
PIA-B0: IC9.23 (A), IC10.23 (A); also elsewhere on the board
PIA-B1: IC9.22 (B), IC10.22 (B); also elsewhere on the board
PIA-B2: IC9.21 (C), IC10.21 (C); also elsewhere on the board
PIA-B3: IC9.20 (D), IC10.20 (D); also elsewhere on the board
PIA-B4: IC9.18 (G1); also elsewhere on the board
PIA-B5: IC10.18 (G1); also elsewhere on the board
VCC: BYP1.1, BYP2.1, BYP3.1, BYP4.1, BYP5.1, BYP6.1, BYP7.1, BYP8.1, BYP9.1, BYP10.1, BYP11.1, BYP12.1, BYP13.1, BYP14.1, BYP15.1, BYP16.1, BYP17.1, IC1.20 (VCC), IC2.20 (VCC), IC3.20 (VCC), IC4.20 (VCC), IC5.20 (VCC), IC6.20 (VCC), IC7.20 (VCC), IC8.20 (VCC), IC9.24 (VCC), IC10.24 (VCC), IC11.11 (ENC), IC11.20 (VCC), IC12.11 (ENC), IC12.20 (VCC), IC13.11 (ENC), IC13.20 (VCC), IC14.11 (ENC), IC14.20 (VCC), IC15.11 (ENC), IC15.20 (VCC), IC16.11 (ENC), IC16.20 (VCC); also elsewhere on the board
